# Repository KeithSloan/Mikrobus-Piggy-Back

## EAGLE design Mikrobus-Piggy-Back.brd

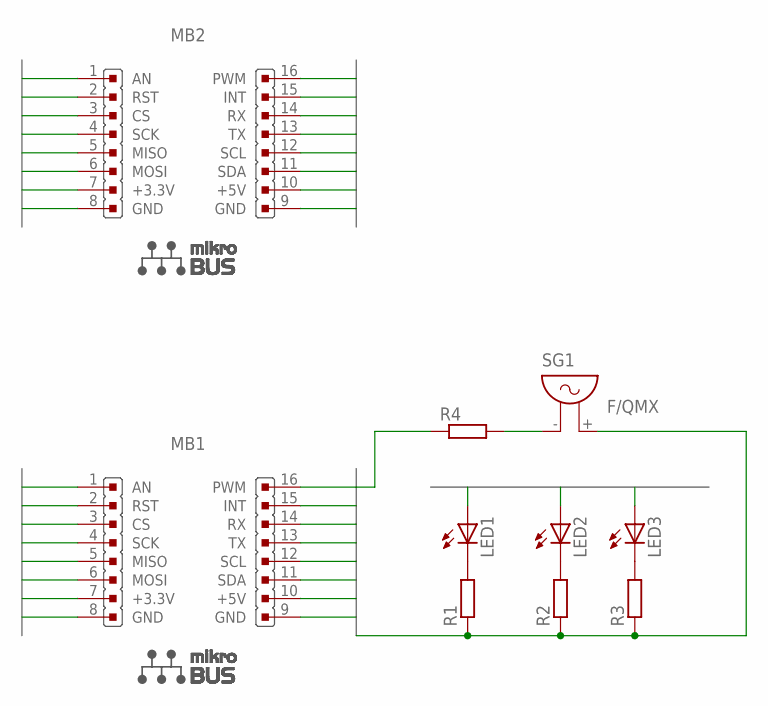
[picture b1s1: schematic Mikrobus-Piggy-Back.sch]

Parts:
LED1, LED2, LED3: LED3MM
MB1, MB2: MIKROBUS
R1, R2, R3, R4: R-EU_0204/5; 0204/5
SG1: F/QMX

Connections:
+3V3: MB1.7 (+3.3V), MB2.7 (+3.3V)
+5V: MB1.10 (+5V), MB2.10 (+5V)
AN: MB1.1 (AN), MB2.1 (AN)
CS: MB1.3 (CS), MB2.3 (CS)
GND: MB1.8 (GND), MB1.9 (GND), MB2.8 (GND), MB2.9 (GND), R1.1, R2.1, R3.1, SG1.+ (2)
INT: MB1.15 (INT), MB2.15 (INT)
MISO: MB1.5 (MISO), MB2.5 (MISO)
MOSI: MB1.6 (MOSI), MB2.6 (MOSI)
unnamed: LED1.K (C), R1.2
unnamed: LED2.K (C), R2.2
unnamed: LED3.K (C), R3.2
unnamed: R4.2, SG1.- (1)
PWM: MB1.16 (PWM), MB2.16 (PWM), R4.1
RST: MB1.2 (RST), MB2.2 (RST)
RX: LED1.A, MB1.14 (RX), MB2.14 (RX)
SCK: MB1.4 (SCK), MB2.4 (SCK)
SCL: LED3.A, MB1.12 (SCL), MB2.12 (SCL)
SDA: MB1.11 (SDA), MB2.11 (SDA)
TX: LED2.A, MB1.13 (TX), MB2.13 (TX)

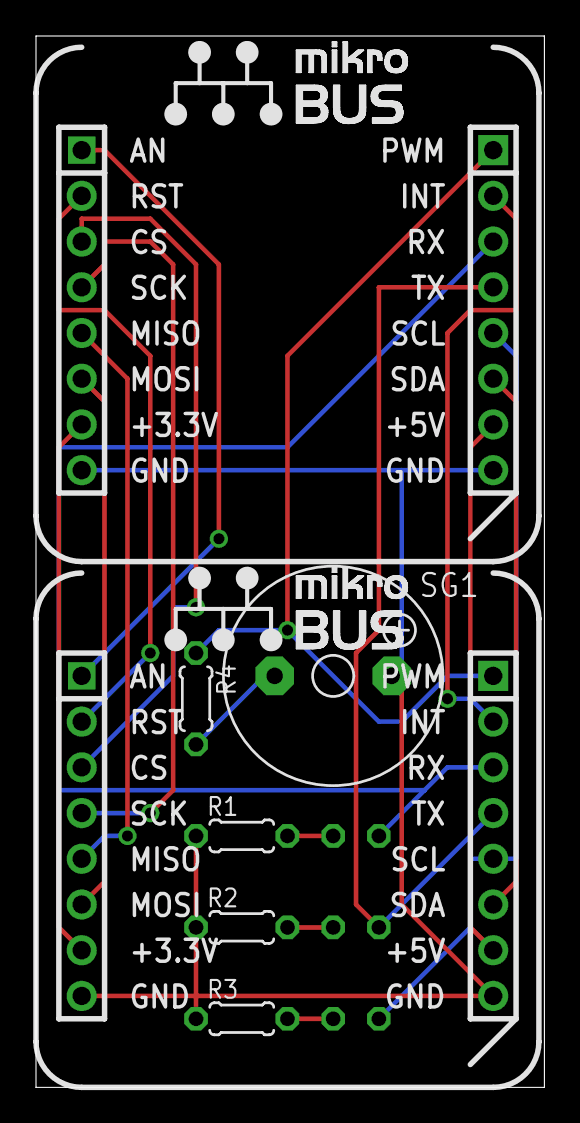
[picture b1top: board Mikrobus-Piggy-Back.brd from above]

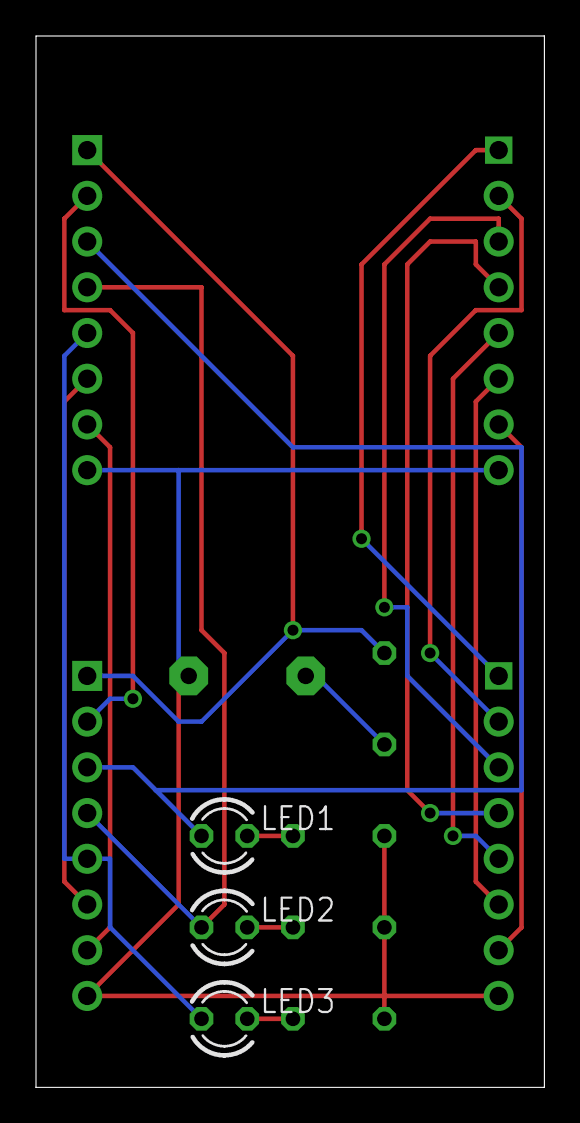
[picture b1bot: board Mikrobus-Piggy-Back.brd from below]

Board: 2 copper layers, 28.2 x 58.4 mm, 10 parts (3 on the bottom side), 19 nets.

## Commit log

2016-11-05 Add files
